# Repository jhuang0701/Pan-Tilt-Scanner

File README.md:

# Pan-Tilt Scanner Controller

A two-axis pan/tilt scanner controller designed in KiCad. The project includes the schematic, PCB, a schematic PDF export, a grouped bill of materials, and fabrication outputs. The supplied project files show two Pololu A4988 stepper-driver carrier modules controlled by an STM32F103C8Tx.

## What it does

The board provides control and power circuitry for two stepper-driven axes. An STM32F103C8Tx microcontroller interfaces with two Pololu A4988 carrier modules. An LM2596S-5 switching regulator and an AP2112K-3.3 linear regulator provide the board's 5 V and 3.3 V rails.

## Core components

- **Microcontroller:** STM32F103C8Tx (U3), the board's central controller.
- **Stepper drivers:** Two Pololu A4988 carrier modules (A2 and A3), for the two motion axes.
- **5 V regulator:** LM2596S-5 (U1), a switching regulator.
- **3.3 V regulator:** AP2112K-3.3 (U2), a linear regulator.
- **Clock:** Crystal Y1 with two 20 pF capacitors.

## Design decisions worth knowing about

- The design uses two Pololu A4988 carrier modules rather than placing the stepper-driver ICs directly on the PCB.
- The power section provides 5 V and 3.3 V regulated rails using separate switching and linear regulator devices.
- The PCB stackup defines front and back copper layers and a nominal total board thickness of 1.6 mm.

## Specs

| Specification | Verified value |
| --- | --- |
| Stepper-driver interfaces | 2 x Pololu A4988 carrier modules |
| Regulated rails | +5 V, +3.3 V |
| Copper layers | 2 |
| Board thickness | 1.6 mm |

## Repo contents

- [`schematic/`](schematic/) - KiCad schematic, PCB, project settings, and one-page schematic PDF export.
- [`gerbers/`](gerbers/) - Gerber layers, plated and non-plated drill files, Gerber job file, and the supplied ZIP bundle. The ZIP contains byte-identical copies of the individual Gerber and drill files.
- [`bom/`](bom/) - Grouped bill of materials CSV.
- [`public/`](public/) - Presentation screenshots: [3D board view, angle 1](public/pan-tilt-scanner-3d-angle-1.png), [3D board view, angle 2](public/pan-tilt-scanner-3d-angle-2.png), and [2D PCB layout](public/pan-tilt-scanner-pcb-2d-layout.png).

The root-level [pan_tilt_scanner-all-pos.csv](pan_tilt_scanner-all-pos.csv) is a component placement export, not a bill of materials. No separate render assets were present, so there is no `render/` folder.

## Status

The KiCad schematic and PCB files, a schematic PDF, and fabrication exports are present. DRC status has not been verified, and the repository contains no confirmation of fabrication or assembly.

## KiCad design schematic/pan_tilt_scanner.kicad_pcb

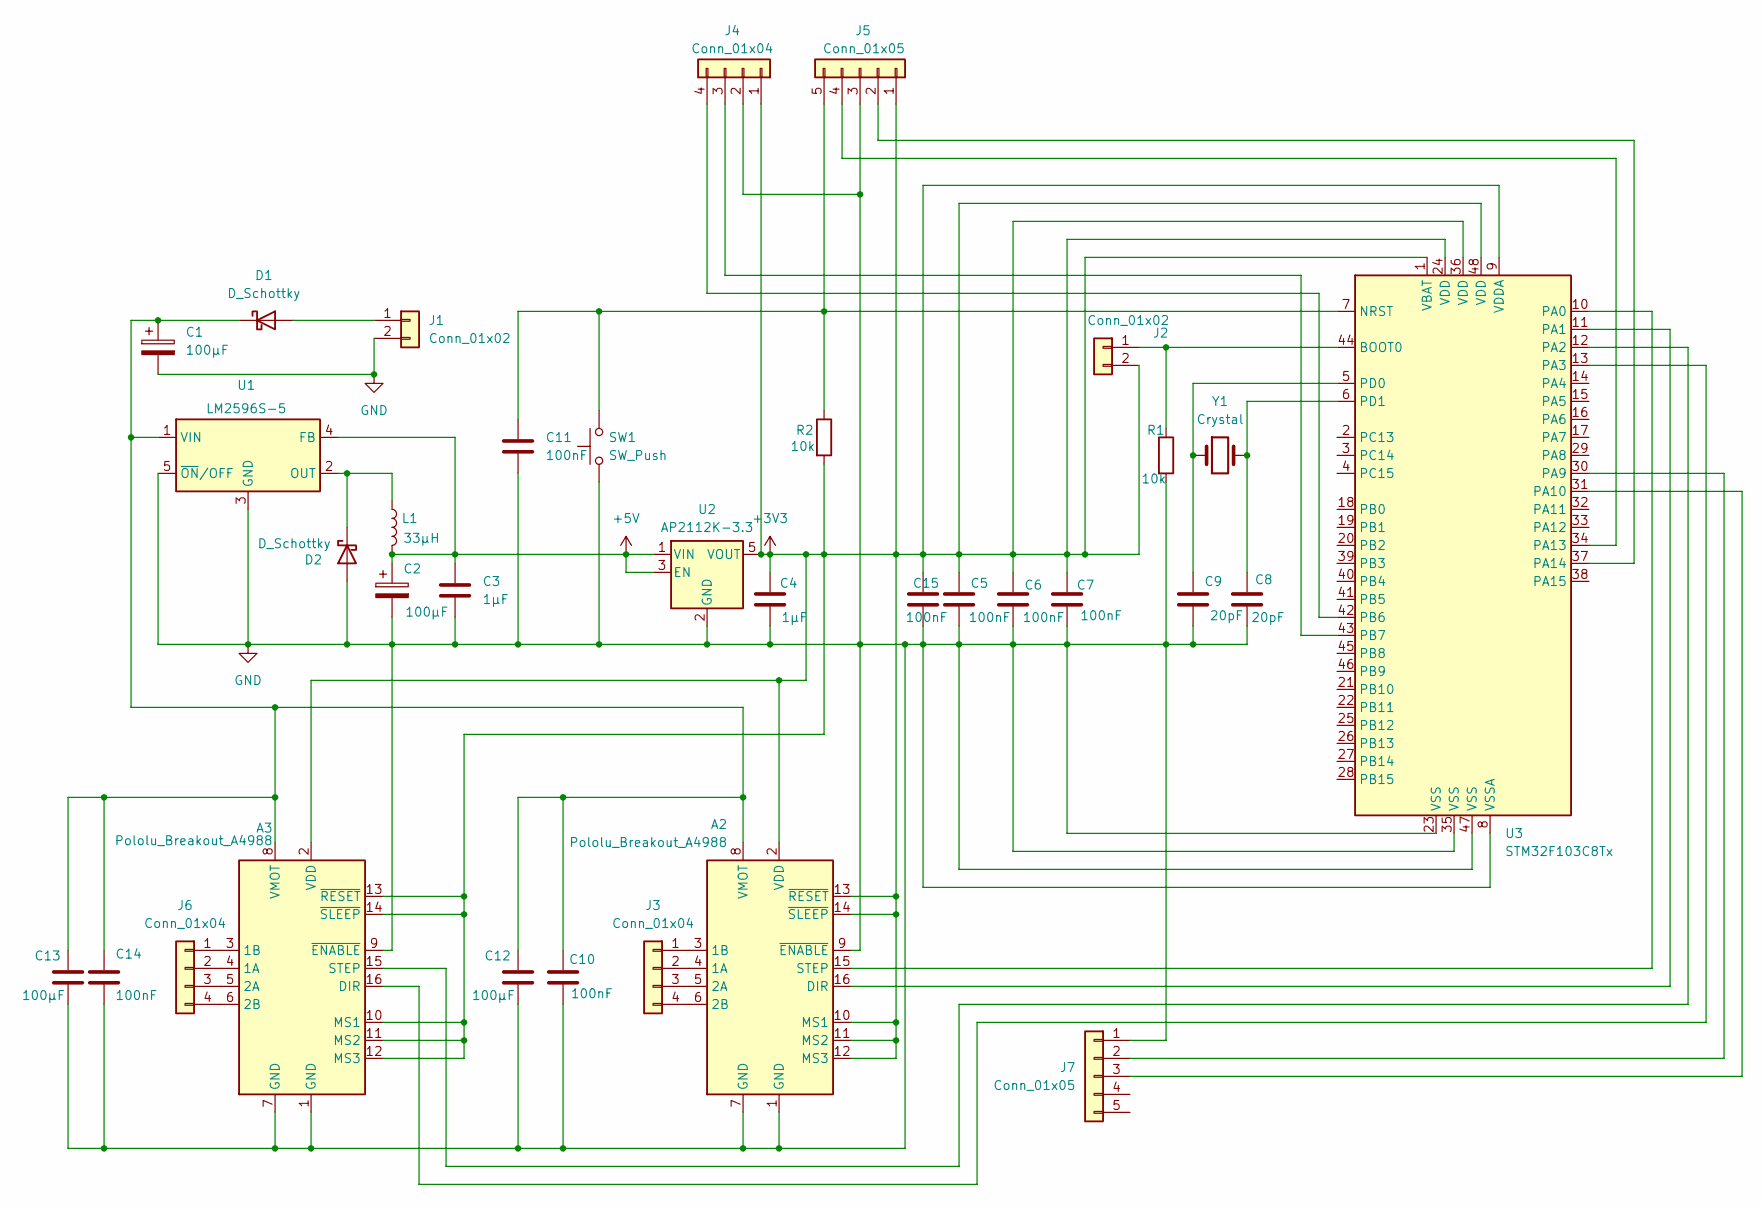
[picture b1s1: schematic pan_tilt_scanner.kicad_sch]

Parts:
A2, A3: Pololu_Breakout_A4988; Pololu_Breakout-16_15.2x20.3mm
C1, C2, C12, C13: 100µF; CP_Radial_D6.3mm_P2.50mm
C3, C4: 1µF; C_0805_2012Metric
C5, C6, C7, C10, C11, C14, C15: 100nF; C_0805_2012Metric
C8, C9: 20pF; C_0805_2012Metric
D1, D2: D_Schottky; D_SMA
J1, J2: Conn_01x02; PinHeader_1x02_P2.54mm_Vertical
J3, J4, J6: Conn_01x04; PinHeader_1x04_P2.54mm_Vertical
J5: Conn_01x05; PinHeader_1x05_P2.54mm_Vertical
J7: Conn_01x05; PinSocket_1x05_P2.54mm_Vertical
L1: 33µH; L_12x12mm_H8mm
R1, R2: 10k; R_0805_2012Metric
SW1: SW_Push; SW_PUSH_6mm
U1: LM2596S-5; TO-263-5_TabPin3
U2: AP2112K-3.3; SOT-23-5
U3: STM32F103C8Tx; LQFP-48_7x7mm_P0.5mm
Y1: Crystal; Crystal_SMD_3225-4Pin_3.2x2.5mm

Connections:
+3V3: A2.2 (VDD), A2.10 (MS1), A2.11 (MS2), A2.12 (MS3), A2.13 (~RESET), A2.14 (~SLEEP), A3.2 (VDD), A3.10 (MS1), A3.11 (MS2), A3.12 (MS3), A3.13 (~RESET), A3.14 (~SLEEP), C4.1, C5.1, C6.1, C7.1, C15.1, J2.2, J4.1, J5.1, R2.2, U2.5 (VOUT), U3.1 (VBAT), U3.9 (VDDA), U3.24 (VDD), U3.36 (VDD), U3.48 (VDD)
+5V: C2.1, C3.1, L1.2, U1.4 (FB), U2.1 (VIN), U2.3 (EN)
GND: A2.1 (GND), A2.7 (GND), A2.9 (~ENABLE), A3.1 (GND), A3.7 (GND), A3.9 (~ENABLE), C1.2, C2.2, C3.2, C4.2, C5.2, C6.2, C7.2, C8.2, C9.2, C10.2, C11.2, C12.2, C13.2, C14.2, C15.2, D2.2 (A), J1.2, J4.2, J5.3, J7.1, R1.2, SW1.1, U1.3 (GND), U1.5 (~ON/OFF), U2.2 (GND), U3.8 (VSSA), U3.23 (VSS), U3.35 (VSS), U3.47 (VSS)
unnamed: A2.4 (1A), J3.2
unnamed: A2.3 (1B), J3.1
unnamed: A2.5 (2A), J3.3
unnamed: A2.6 (2B), J3.4
unnamed: A2.16 (DIR), U3.11 (PA1)
unnamed: A2.15 (STEP), U3.10 (PA0)
unnamed: A2.8 (VMOT), A3.8 (VMOT), C1.1, C10.1, C12.1, C13.1, C14.1, D1.1 (K), U1.1 (VIN)
unnamed: A3.4 (1A), J6.2
unnamed: A3.3 (1B), J6.1
unnamed: A3.5 (2A), J6.3
unnamed: A3.6 (2B), J6.4
unnamed: A3.16 (DIR), U3.13 (PA3)
unnamed: A3.15 (STEP), U3.12 (PA2)
unnamed: D1.2 (A), J1.1
unnamed: D2.1 (K), L1.1, U1.2 (OUT)
unnamed: J2.1, R1.1, U3.44 (BOOT0)
unnamed: J4.3, U3.43 (PB7)
unnamed: J4.4, U3.42 (PB6)
unnamed: J5.2, U3.37 (PA14)
unnamed: J5.4, U3.34 (PA13)
unnamed: C11.1, J5.5, R2.1, SW1.2, U3.7 (NRST)
unnamed: J7.2, U3.30 (PA9)
unnamed: J7.3, U3.31 (PA10)
unnamed: C9.1, U3.5 (PD0), Y1.1
unnamed: C8.1, U3.6 (PD1), Y1.2

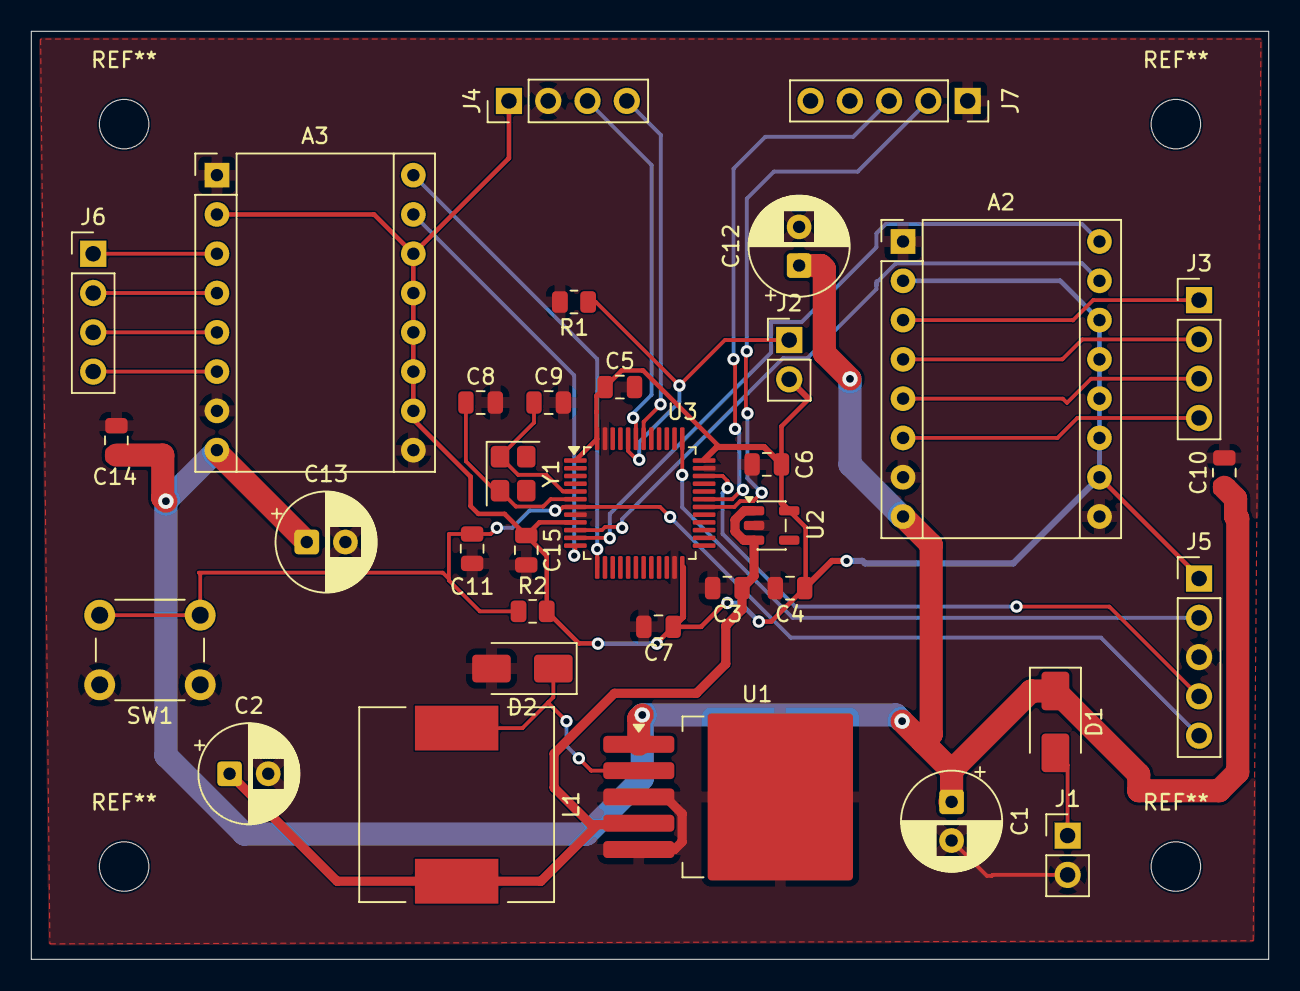
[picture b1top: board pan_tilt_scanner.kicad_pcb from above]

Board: 2 copper layers, 80.0 x 60.0 mm, 34 parts (0 on the bottom side), 28 nets.
